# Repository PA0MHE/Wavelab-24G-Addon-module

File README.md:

# Wavelab addon module

Can be used as addon module for the Wavelab 23X1008XP module, which was available during the 2021-2022 timeframe on www.ebay.pl seller:bisonelectronics-sp2jyr
The module converts the first-IF 2364MHz to 432MHz (or 144MHz) , it als generates the required first LO of 1807MHz. It also generates all required DC value, such as 6.5V, +5V, -5V, also the required RX-TX switching is provided. 
The module requires a 10MHz reference signal, it has to be supplied with 7.5V DC. 

# Key components:

HMC213B
2x AS179-92LF
LFB2H2G45SG7C093
2x ADF4351
2x MIC29302
2x BD50HC5MEFJ
ADM7150/1  
ATtiny85-20S  

# PCB

Gerber files are included, PCB's can be ordered at JCL PCB substrate thickness is 0.8mm 

73's Maarten PA0MHE

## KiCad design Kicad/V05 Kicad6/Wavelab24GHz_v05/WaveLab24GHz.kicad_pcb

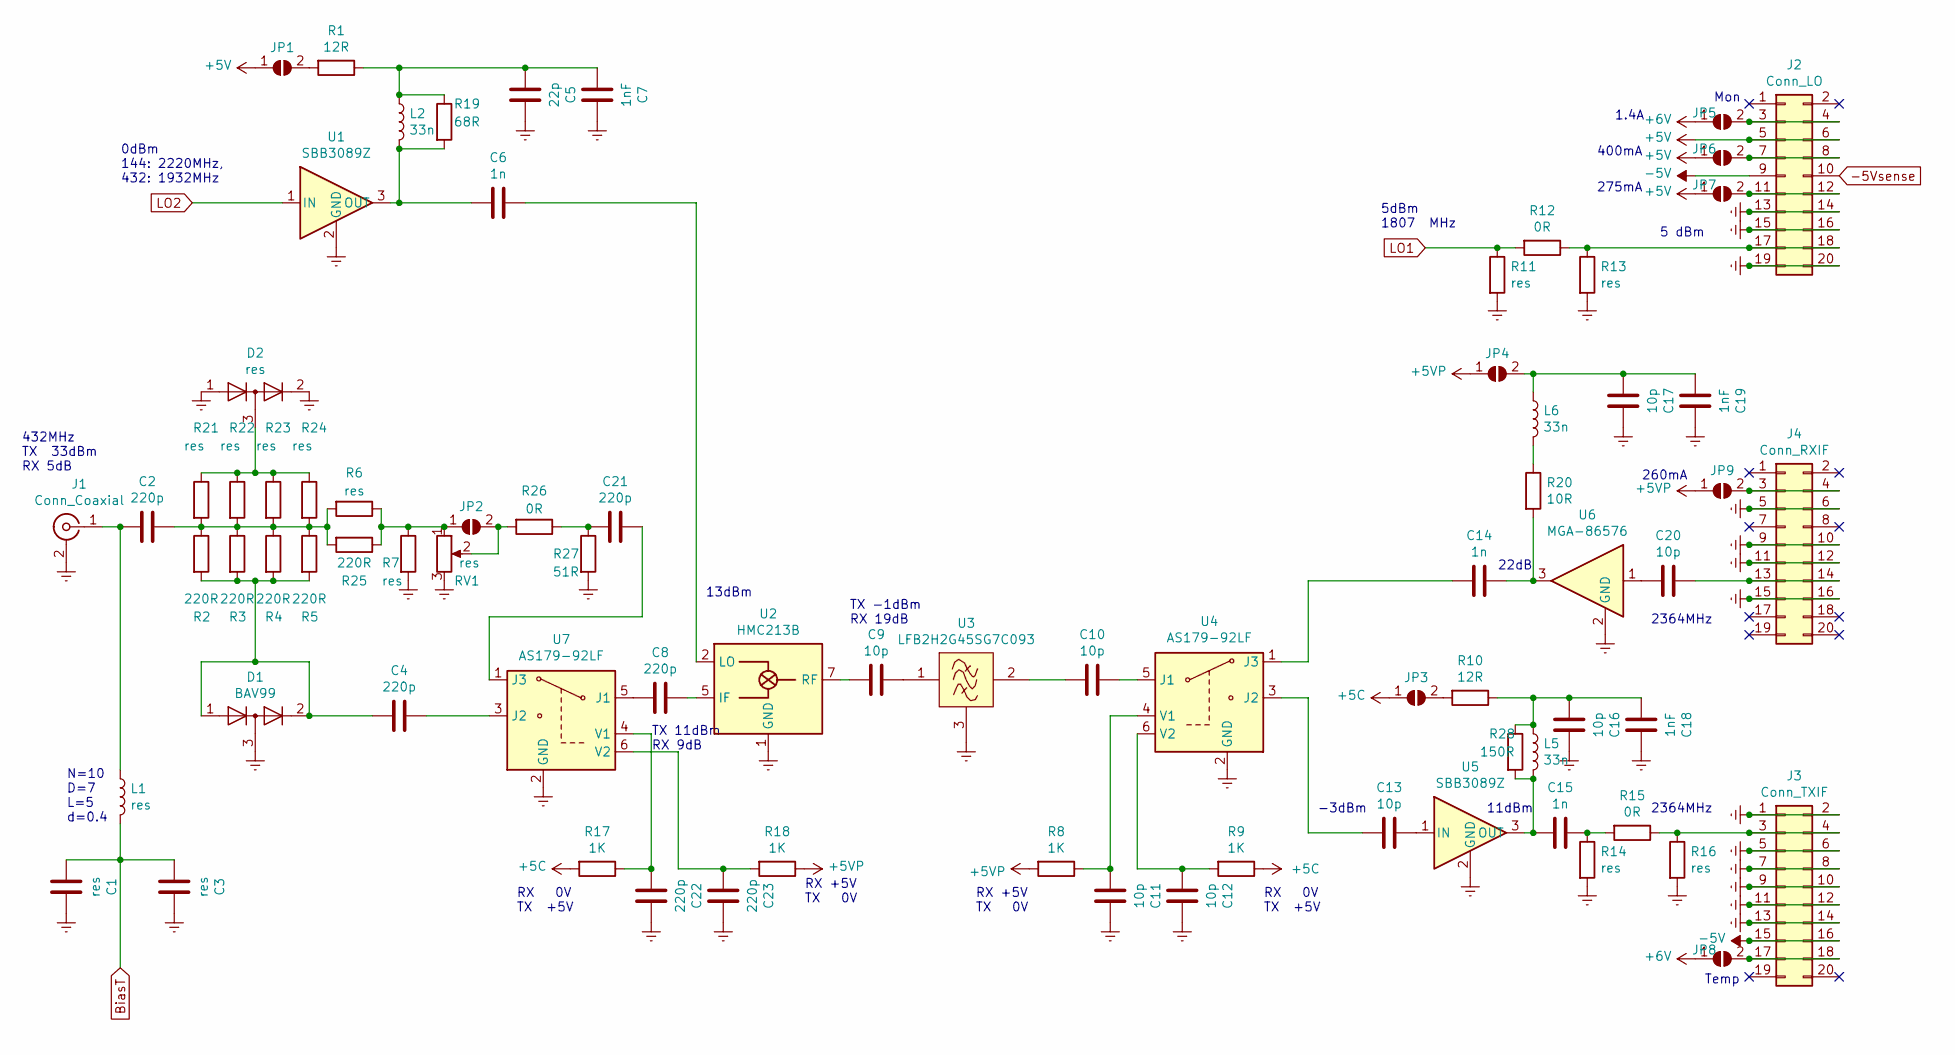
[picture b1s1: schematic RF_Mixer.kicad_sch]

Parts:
C1, C3: res; C_0805_2012Metric_Pad1.18x1.45mm_HandSolder
C2, C4, C8, C21, C22, C23: 220p; C_0805_2012Metric_Pad1.18x1.45mm_HandSolder
C5: 22p; C_0805_2012Metric_Pad1.18x1.45mm_HandSolder
C6, C14, C15: 1n; C_0805_2012Metric_Pad1.18x1.45mm_HandSolder
C7, C18, C19: 1nF; C_0805_2012Metric_Pad1.18x1.45mm_HandSolder
C9, C10, C11, C12, C13, C16, C17, C20: 10p; C_0805_2012Metric_Pad1.18x1.45mm_HandSolder
D1: BAV99; SOT-23
D2: res; SOT-23
J1: Conn_Coaxial; SMA_side_PCB
J2: Conn_LO; PinHeader_24GHz-NP
J3: Conn_TXIF; PinHeader_24GHz-NP
J4: Conn_RXIF; PinHeader_24GHz-NP
JP1, JP2, JP3, JP4, JP5, JP6, JP7, JP8, JP9: S; SolderJumper-2_P1.3mm_Open_RoundedPad1.0x1.5mm
L1: res; AirCoilSMD
L2, L5, L6: 33n; L_0805_2012Metric_Pad1.15x1.40mm_HandSolder
R1, R10: 12R; R_0805_2012Metric_Pad1.20x1.40mm_HandSolder
R2, R3, R4, R5, R25: 220R; R_1206_3216Metric_Pad1.30x1.75mm_HandSolder
R6, R21, R22, R23, R24: res; R_1206_3216Metric_Pad1.30x1.75mm_HandSolder
R7, R11, R13, R14, R16: res; R_0805_2012Metric_Pad1.20x1.40mm_HandSolder
R8, R17, R18: 1K; R_0805_2012Metric_Pad1.20x1.40mm_HandSolder
R9: 1K; R_1206_3216Metric_Pad1.30x1.75mm_HandSolder
R12: 0R; R_1206_3216Metric_Pad1.30x1.75mm_HandSolder
R15, R26: 0R; R_0805_2012Metric_Pad1.20x1.40mm_HandSolder
R19: 68R; R_0805_2012Metric_Pad1.20x1.40mm_HandSolder
R20: 10R; R_0805_2012Metric_Pad1.20x1.40mm_HandSolder
R27: 51R; R_0805_2012Metric_Pad1.20x1.40mm_HandSolder
R28: 150R; R_0805_2012Metric_Pad1.20x1.40mm_HandSolder
RV1: res; Potentiometer_Vishay_TS53YJ_Vertical
U1, U5: SBB3089Z; SOT-89-3
U2: HMC213B; MSOP-8_3x3mm_P0.65mm
U3: LFB2H2G45SG7C093; LFSN25N
U4, U7: AS179-92LF; SOT-363_SC-70-6
U6: MGA-86576

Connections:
+5C: JP3.1 (A), R9.1, R17.2; also elsewhere on the board
+5V: J2.5, J2.6, JP1.1 (A), JP6.1 (A), JP7.1 (A); also elsewhere on the board
+6V: JP5.1 (A), JP8.1 (A); also elsewhere on the board
-5V: J2.9, J3.15, J3.16; also elsewhere on the board
-5Vsense: J2.10; also elsewhere on the board
BiasT: C1.2, C3.2, L1.2; also elsewhere on the board
GNDREF: C1.1, C3.1, C5.1, C7.1, C11.1, C12.1, C16.1, C17.1, C18.1, C19.1, C22.1, C23.1, D1.3 (K), D2.1 (K), D2.2 (A), J1.2 (Ext), J2.13, J2.14, J2.15, J2.16, J2.19, J2.20, J3.1, J3.2, J3.5, J3.6, J3.7, J3.8, J3.9, J3.10, J3.11, J3.12, J3.13, J3.14, J4.5, J4.6, J4.9, J4.10, J4.11, J4.12, J4.15, J4.16, R7.2, R11.2, R13.2, R14.2, R16.2, R27.2, RV1.3, U1.2 (GND), U2.1 (GND), U2.3 (GND), U2.6 (GND), U2.8 (GND), U3.3, U3.4, U4.2 (GND), U5.2 (GND), U6.2 (GND), U7.2 (GND); also elsewhere on the board
LO1: R11.1, R12.2; also elsewhere on the board
LO2: U1.1 (IN); also elsewhere on the board
unnamed: C2.1, R2.1, R3.1, R4.1, R5.1, R6.2, R21.2, R22.2, R23.2, R24.2, R25.2
unnamed: C2.2, J1.1 (In), L1.1
unnamed: C4.1, U7.3 (J2)
unnamed: C4.2, D1.1 (K), D1.2 (A), R2.2, R3.2, R4.2, R5.2
unnamed: C5.2, C7.2, L2.1, R1.1, R19.1
unnamed: C6.1, U2.2 (LO)
unnamed: C6.2, L2.2, R19.2, U1.3 (OUT)
unnamed: C8.1, U2.5 (IF)
unnamed: C8.2, U7.5 (J1)
unnamed: C9.1, U3.1
unnamed: C9.2, U2.7 (RF)
unnamed: C10.1, U4.5 (J1)
unnamed: C10.2, U3.2
unnamed: C11.2, R8.1, U4.4 (V1)
unnamed: C12.2, R9.2, U4.6 (V2)
unnamed: C13.1, U5.1 (IN)
unnamed: C13.2, U4.3 (J2)
unnamed: C14.1, R20.2, U6.3
unnamed: C14.2, U4.1 (J3)
unnamed: C15.1, R14.1, R15.2
unnamed: C15.2, L5.2, R28.2, U5.3 (OUT)
unnamed: C16.2, C18.2, L5.1, R10.1, R28.1
unnamed: C17.2, C19.2, JP4.2 (B), L6.1
unnamed: C20.1, J4.13, J4.14
unnamed: C20.2, U6.1
unnamed: C21.1, U7.1 (J3)
unnamed: C21.2, R26.1, R27.1
unnamed: C22.2, R17.1, U7.4 (V1)
unnamed: C23.2, R18.2, U7.6 (V2)
unnamed: D2.3 (K), R21.1, R22.1, R23.1, R24.1
unnamed: J2.3, J2.4, JP5.2 (B)
unnamed: J2.7, J2.8, JP6.2 (B)
unnamed: J2.11, J2.12, JP7.2 (B)
unnamed: J2.17, J2.18, R12.1, R13.1
unnamed: J3.3, J3.4, R15.1, R16.1
unnamed: J3.17, J3.18, JP8.2 (B)
unnamed: J4.3, J4.4, JP9.2 (B)
unnamed: JP1.2 (B), R1.2
unnamed: JP2.1 (A), R6.1, R7.1, R25.1, RV1.1
unnamed: JP2.2 (B), R26.2, RV1.2
unnamed: JP3.2 (B), R10.2
unnamed: L6.2, R20.1

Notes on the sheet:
TX 11dBm RX 9dB
260mA
Temp
RX +5V TX 0V
275mA
11dBm
-3dBm
432MHz TX 33dBm RX 5dB
22dB
TX -1dBm RX 19dB
1.4A
N=10 D=7 L=5 d=0.4
0dBm 144: 2220MHz, 432: 1932MHz
2364MHz
RX 0V TX +5V
Mon
400mA
13dBm
2364MHz
5 dBm
5dBm 1807 MHz

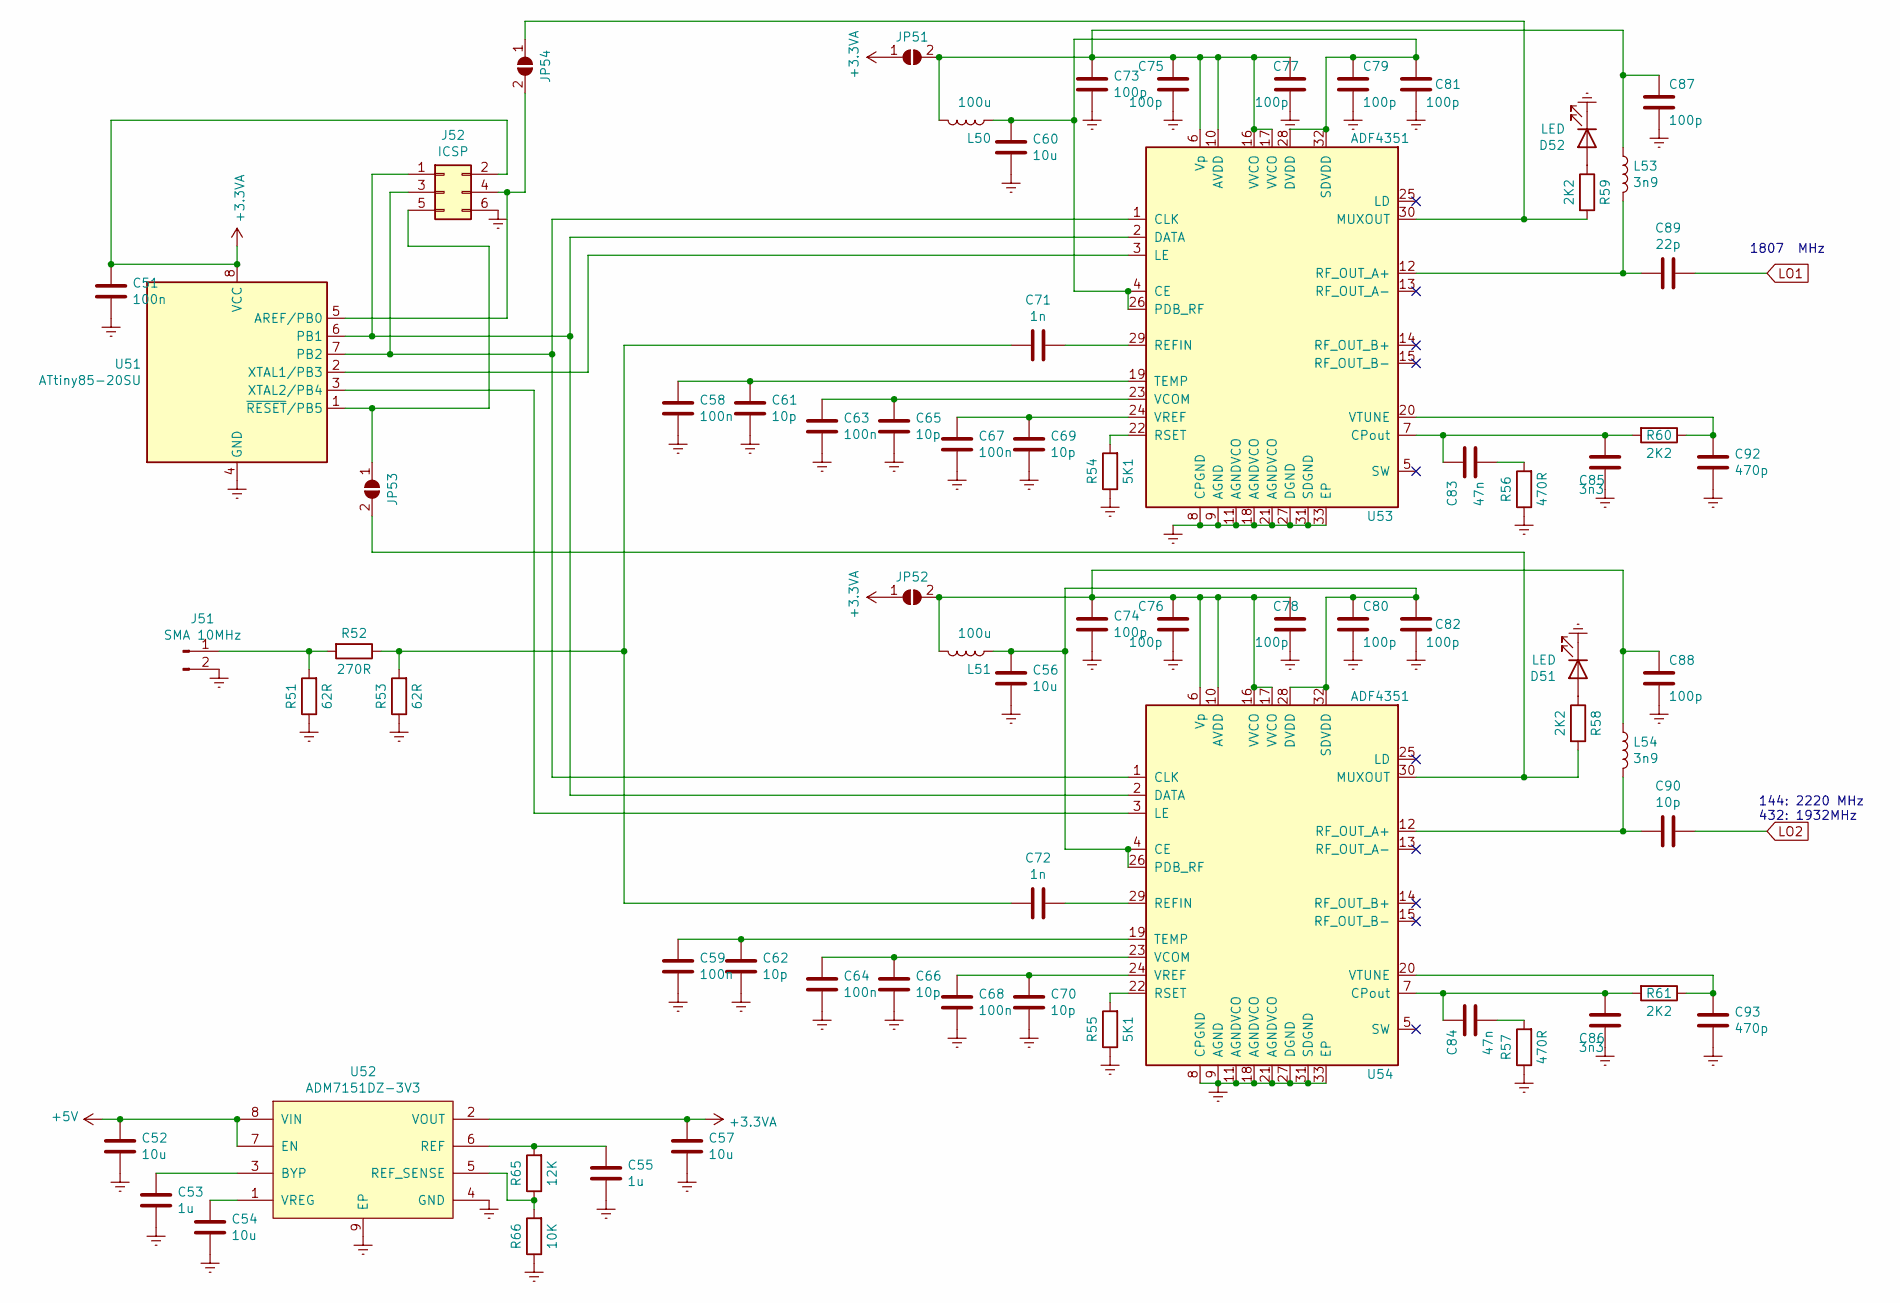
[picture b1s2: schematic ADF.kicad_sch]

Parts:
C51, C58, C59, C63, C64, C67, C68: 100n; C_0805_2012Metric_Pad1.18x1.45mm_HandSolder
C52, C54, C56, C57, C60: 10u; C_0805_2012Metric_Pad1.18x1.45mm_HandSolder
C53, C55: 1u; C_0805_2012Metric_Pad1.18x1.45mm_HandSolder
C61, C62, C65, C66, C69, C70: 10p; C_0603_1608Metric_Pad1.08x0.95mm_HandSolder
C71, C72: 1n; C_0805_2012Metric_Pad1.18x1.45mm_HandSolder
C73, C74, C75, C76, C77, C78, C79, C80, C81, C82: 100p; C_0603_1608Metric_Pad1.08x0.95mm_HandSolder
C83, C84: 47n; C_0805_2012Metric_Pad1.18x1.45mm_HandSolder
C85, C86: 3n3; C_0805_2012Metric_Pad1.18x1.45mm_HandSolder
C87, C88: 100p; C_0805_2012Metric_Pad1.18x1.45mm_HandSolder
C89: 22p; C_0805_2012Metric_Pad1.18x1.45mm_HandSolder
C90: 10p; C_0805_2012Metric_Pad1.18x1.45mm_HandSolder
C92, C93: 470p; C_0805_2012Metric_Pad1.18x1.45mm_HandSolder
D51, D52: LED; LED_0805_2012Metric_Pad1.15x1.40mm_HandSolder
J51: SMA 10MHz; SMA_side_PCB
J52: ICSP; IDC-Header_2x03_P2.54mm_SMD
JP51, JP52, JP53, JP54: S; SolderJumper-2_P1.3mm_Open_RoundedPad1.0x1.5mm
L50, L51: 100u; L_0805_2012Metric_Pad1.05x1.20mm_HandSolder
L53, L54: 3n9; L_0805_2012Metric_Pad1.05x1.20mm_HandSolder
R51, R53: 62R; R_0805_2012Metric_Pad1.20x1.40mm_HandSolder
R52: 270R; R_0805_2012Metric_Pad1.20x1.40mm_HandSolder
R54, R55: 5K1; R_0805_2012Metric_Pad1.20x1.40mm_HandSolder
R56, R57: 470R; R_0805_2012Metric_Pad1.20x1.40mm_HandSolder
R58, R59, R60, R61: 2K2; R_0805_2012Metric_Pad1.20x1.40mm_HandSolder
R65: 12K; R_0805_2012Metric_Pad1.20x1.40mm_HandSolder
R66: 10K; R_0805_2012Metric_Pad1.20x1.40mm_HandSolder
U51: ATtiny85-20SU; SOIJ-8_5.3x5.3mm_P1.27mm
U52: ADM7151DZ-3V3; SOIC-8-1EP_3.9x4.9mm_P1.27mm_EP2.29x3mm_ThermalVias
U53, U54: ADF4351; LFCSP-32-1EP_5x5mm_P0.5mm_EP3.1x3.1mm_ThermalVias

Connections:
+3.3VA: C51.2, C57.2, J52.2, JP51.1 (A), JP52.1 (A), U51.8 (VCC), U52.2 (VOUT)
+5V: C52.2, U52.7 (EN), U52.8 (VIN); also elsewhere on the board
GNDREF: C51.1, C52.1, C53.1, C54.1, C55.1, C56.1, C57.1, C58.1, C59.1, C60.1, C61.1, C62.1, C63.1, C64.1, C65.1, C66.1, C67.1, C68.1, C69.1, C70.1, C73.1, C74.1, C75.1, C76.1, C77.1, C78.1, C79.1, C80.1, C81.1, C82.1, C85.1, C86.1, C87.1, C88.1, C92.1, C93.1, D51.1 (K), D52.1 (K), J51.2, J52.6, R51.1, R53.1, R54.1, R55.1, R56.1, R57.1, R66.1, U51.4 (GND), U52.4 (GND), U52.9 (EP), U53.8 (CPGND), U53.9 (AGND), U53.11 (AGNDVCO), U53.18 (AGNDVCO), U53.21 (AGNDVCO), U53.27 (DGND), U53.31 (SDGND), U53.33 (EP), U54.8 (CPGND), U54.9 (AGND), U54.11 (AGNDVCO), U54.18 (AGNDVCO), U54.21 (AGNDVCO), U54.27 (DGND), U54.31 (SDGND), U54.33 (EP); also elsewhere on the board
LO1: C89.1; also elsewhere on the board
LO2: C90.1; also elsewhere on the board
unnamed: C53.2, U52.3 (BYP)
unnamed: C54.2, U52.1 (VREG)
unnamed: C55.2, R65.2, U52.6 (REF)
unnamed: C56.2, C80.2, C82.2, L51.1, U54.4 (CE), U54.26 (PDB_RF), U54.28 (DVDD), U54.32 (SDVDD)
unnamed: C58.2, C61.2, U53.19 (TEMP)
unnamed: C59.2, C62.2, U54.19 (TEMP)
unnamed: C60.2, C79.2, C81.2, L50.1, U53.4 (CE), U53.26 (PDB_RF), U53.28 (DVDD), U53.32 (SDVDD)
unnamed: C63.2, C65.2, U53.23 (VCOM)
unnamed: C64.2, C66.2, U54.23 (VCOM)
unnamed: C67.2, C69.2, U53.24 (VREF)
unnamed: C68.2, C70.2, U54.24 (VREF)
unnamed: C71.1, U53.29 (REFIN)
unnamed: C71.2, C72.2, R52.1, R53.2
unnamed: C72.1, U54.29 (REFIN)
unnamed: C73.2, C75.2, C77.2, C87.2, JP51.2 (B), L50.2, L53.1, U53.6 (Vp), U53.10 (AVDD), U53.16 (VVCO), U53.17 (VVCO)
unnamed: C74.2, C76.2, C78.2, C88.2, JP52.2 (B), L51.2, L54.1, U54.6 (Vp), U54.10 (AVDD), U54.16 (VVCO), U54.17 (VVCO)
unnamed: C83.1, R56.2
unnamed: C83.2, C85.2, R60.2, U53.7 (CPout)
unnamed: C84.1, R57.2
unnamed: C84.2, C86.2, R61.2, U54.7 (CPout)
unnamed: C89.2, L53.2, U53.12 (RF_OUT_A+)
unnamed: C90.2, L54.2, U54.12 (RF_OUT_A+)
unnamed: C92.2, R60.1, U53.20 (VTUNE)
unnamed: C93.2, R61.1, U54.20 (VTUNE)
unnamed: D51.2 (A), R58.1
unnamed: D52.2 (A), R59.1
unnamed: J51.1, R51.2, R52.2
unnamed: J52.1, U51.6 (PB1), U53.2 (DATA), U54.2 (DATA)
unnamed: J52.3, U51.7 (PB2), U53.1 (CLK), U54.1 (CLK)
unnamed: J52.4, JP54.2 (B), U51.5 (AREF/PB0)
unnamed: J52.5, JP53.1 (A), U51.1 (~RESET/PB5)
unnamed: JP53.2 (B), R58.2, U54.30 (MUXOUT)
unnamed: JP54.1 (A), R59.2, U53.30 (MUXOUT)
unnamed: R54.2, U53.22 (RSET)
unnamed: R55.2, U54.22 (RSET)
unnamed: R65.1, R66.2, U52.5 (REF_SENSE)
unnamed: U51.2 (XTAL1/PB3), U53.3 (LE)
unnamed: U51.3 (XTAL2/PB4), U54.3 (LE)

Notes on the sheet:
1807 MHz
144: 2220 MHz 432: 1932MHz

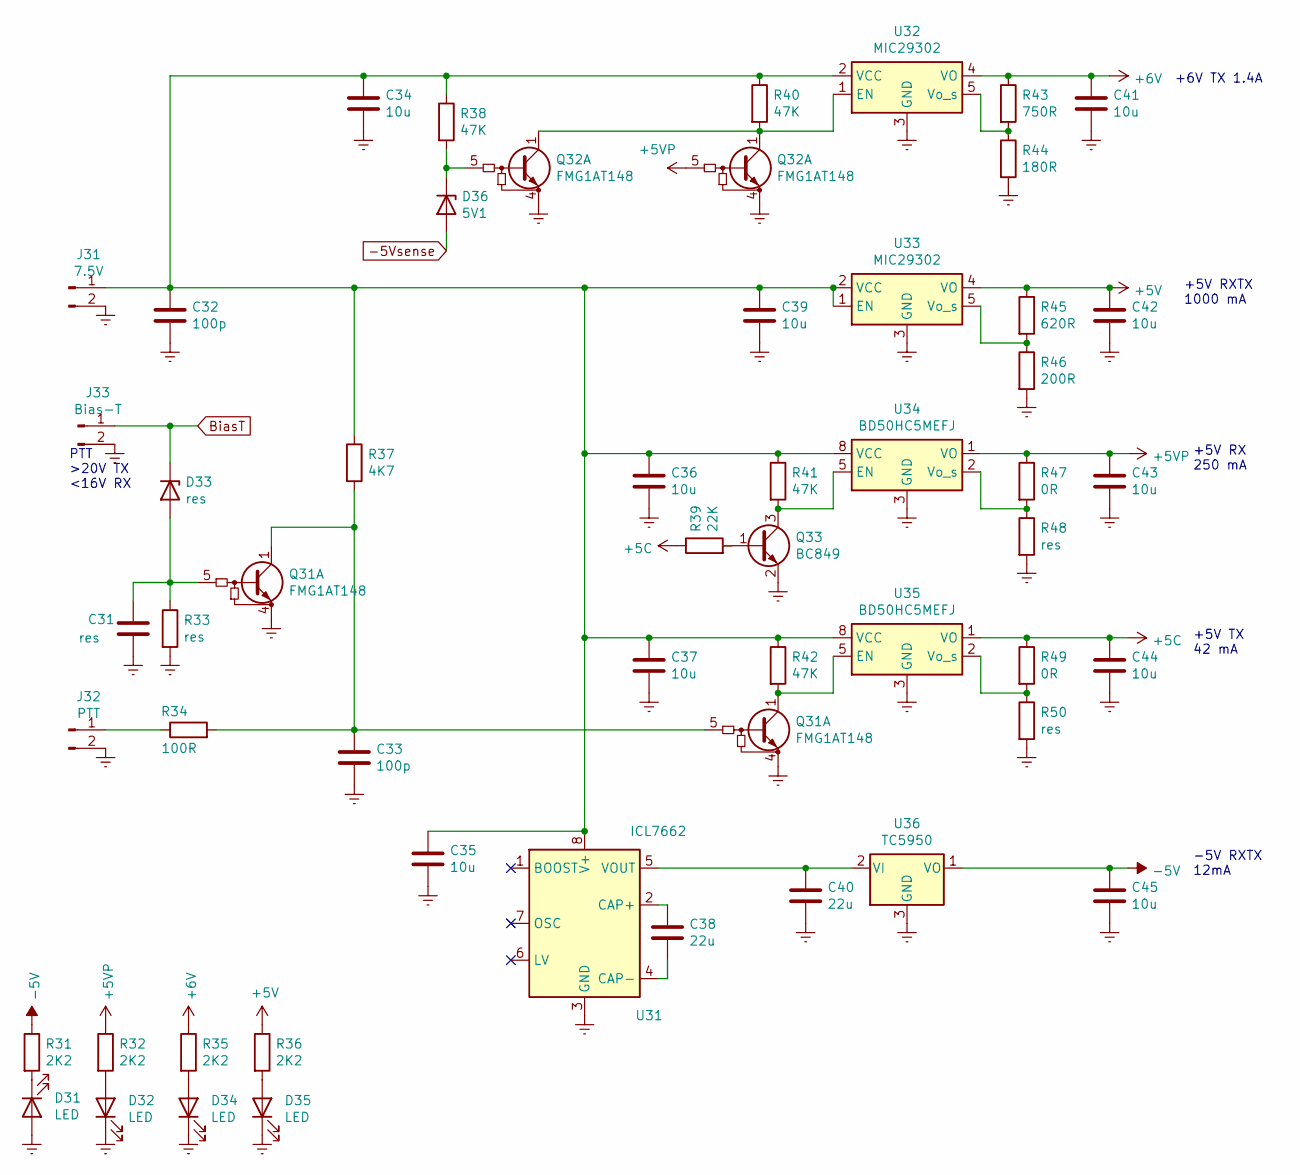
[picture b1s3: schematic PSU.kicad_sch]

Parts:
C31: res; C_0805_2012Metric_Pad1.18x1.45mm_HandSolder
C32, C33: 100p; C_0805_2012Metric_Pad1.18x1.45mm_HandSolder
C34, C35, C36, C37, C39, C41, C42, C43, C44, C45: 10u; C_0805_2012Metric_Pad1.18x1.45mm_HandSolder
C38, C40: 22u; C_0805_2012Metric_Pad1.18x1.45mm_HandSolder
D31, D32, D34, D35: LED; LED_0805_2012Metric_Pad1.15x1.40mm_HandSolder
D33: res; R_0805_2012Metric_Pad1.20x1.40mm_HandSolder
D36: 5V1; R_0805_2012Metric_Pad1.20x1.40mm_HandSolder
J31: 7.5V; KF301-2P-NP
J32: PTT; KF301-2P-NP
J33: Bias-T; KF301-2P-NP
Q31, Q32: FMG1AT148; SOT-25_HandSoldering
Q33: BC849; SOT-23
R31, R32, R35, R36: 2K2; R_0805_2012Metric_Pad1.20x1.40mm_HandSolder
R33, R48, R50: res; R_0805_2012Metric_Pad1.20x1.40mm_HandSolder
R34: 100R; R_0805_2012Metric_Pad1.20x1.40mm_HandSolder
R37: 4K7; R_0805_2012Metric_Pad1.20x1.40mm_HandSolder
R38, R40, R41, R42: 47K; R_0805_2012Metric_Pad1.20x1.40mm_HandSolder
R39: 22K; R_0805_2012Metric_Pad1.20x1.40mm_HandSolder
R43: 750R; R_0805_2012Metric_Pad1.20x1.40mm_HandSolder
R44: 180R; R_0805_2012Metric_Pad1.20x1.40mm_HandSolder
R45: 620R; R_0805_2012Metric_Pad1.20x1.40mm_HandSolder
R46: 200R; R_0805_2012Metric_Pad1.20x1.40mm_HandSolder
R47, R49: 0R; R_0805_2012Metric_Pad1.20x1.40mm_HandSolder
U31: ICL7662; SOIC-8_3.9x4.9mm_P1.27mm
U32, U33: MIC29302; TO-263-5_TabPin6
U34, U35: BD50HC5MEFJ; HTSOP-8-1EP_3.9x4.9mm_P1.27mm_EP2.4x3.2mm
U36: TC5950; SOT-23

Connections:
+5C: C44.1, R39.1, R49.1, U35.1 (VO); also elsewhere on the board
+5V: C42.1, R36.1, R45.1, U33.4 (VO); also elsewhere on the board
+6V: C41.1, R35.1, R43.1, U32.4 (VO); also elsewhere on the board
-5V: C45.1, R31.1, U36.1 (VO); also elsewhere on the board
-5Vsense: D36.2 (A); also elsewhere on the board
BiasT: D33.1 (K), J33.1; also elsewhere on the board
GNDREF: C31.2, C32.2, C33.2, C34.2, C35.2, C36.2, C37.2, C39.2, C40.2, C41.2, C42.2, C43.2, C44.2, C45.2, D31.2 (A), D32.1 (K), D34.1 (K), D35.1 (K), J31.2, J32.2, J33.2, Q31.4 (E1), Q32.4 (E1), Q33.2 (E), R33.2, R44.2, R46.2, R48.2, R50.2, U31.3 (GND), U32.3 (GND), U32.6 (GND), U33.3 (GND), U33.6 (GND), U34.3 (GND), U34.4 (GND), U34.6 (GND), U34.7 (GND), U34.9 (GND), U35.3 (GND), U35.4 (GND), U35.6 (GND), U35.7 (GND), U35.9 (GND), U36.3 (GND); also elsewhere on the board
unnamed: C32.1, C34.1, C35.1, C36.1, C37.1, C39.1, J31.1, R37.1, R38.1, R40.1, R41.1, R42.1, U31.8 (V+), U32.2 (VCC), U33.1 (EN), U33.2 (VCC), U34.8 (VCC), U35.8 (VCC)
unnamed: C38.1, U31.2 (CAP+)
unnamed: C38.2, U31.4 (CAP-)
unnamed: C40.1, U31.5 (VOUT), U36.2 (VI)
unnamed: D31.1 (K), R31.2
unnamed: D32.2 (A), R32.2
unnamed: D34.2 (A), R35.2
unnamed: D35.2 (A), R36.2
unnamed: J32.1, R34.1
unnamed: Q32.1 (C1), Q32.2 (C1), R40.2, U32.1 (EN)
unnamed: Q33.1 (B), R39.2
unnamed: Q33.3 (C), R41.2, U34.5 (EN)
unnamed: R43.2, R44.1, U32.5 (Vo_s)
unnamed: R45.2, R46.1, U33.5 (Vo_s)
unnamed: R47.2, R48.1, U34.2 (Vo_s)
unnamed: R49.2, R50.1, U35.2 (Vo_s)

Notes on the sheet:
+6V TX 1.4A
+5V RX 250 mA
+5V RXTX 1000 mA
PTT >20V TX <16V RX
+5V TX 42 mA
-5V RXTX 12mA

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
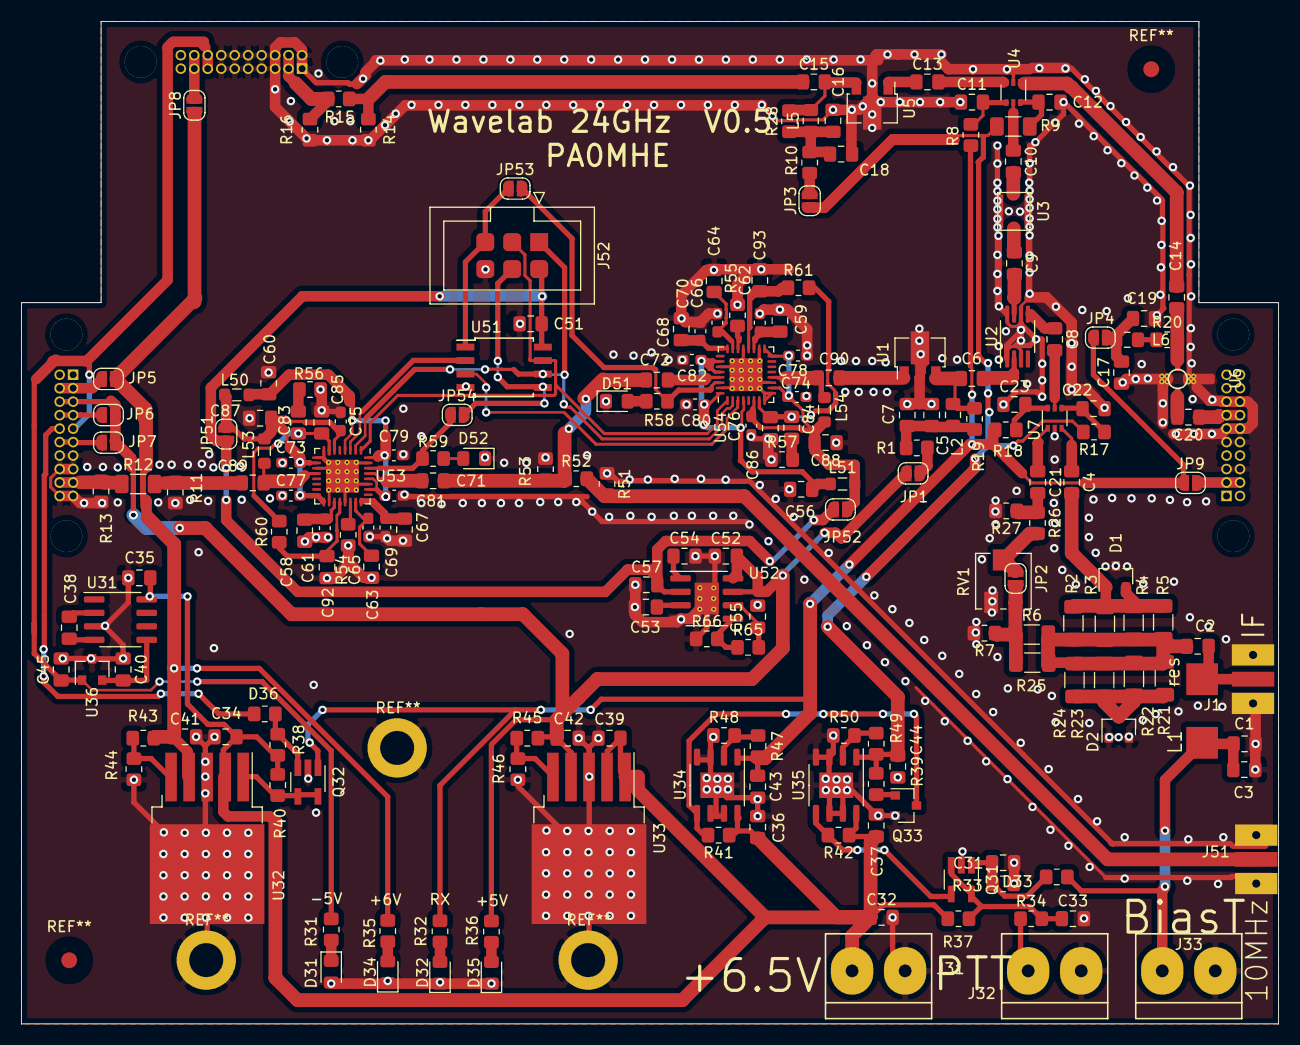
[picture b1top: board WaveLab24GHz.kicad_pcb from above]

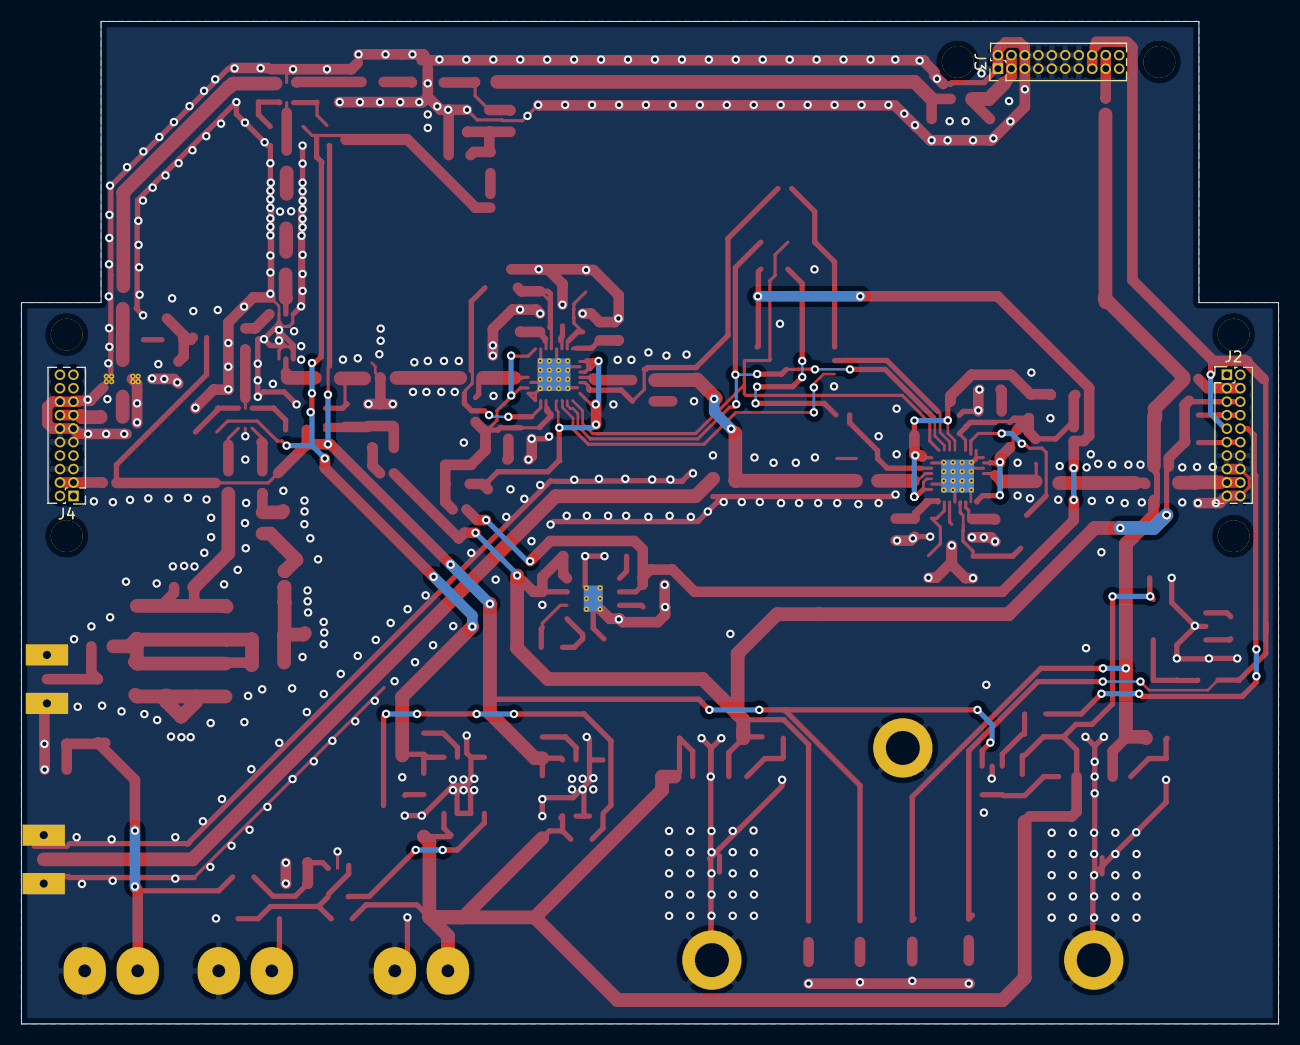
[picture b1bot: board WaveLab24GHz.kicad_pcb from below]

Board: 2 copper layers, 118.5 x 94.5 mm, 202 parts (3 on the bottom side), 111 nets.

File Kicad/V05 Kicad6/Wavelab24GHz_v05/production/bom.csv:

Designator,Footprint,Quantity,Value,LCSC Part #
C1,C_0805_2012Metric_Pad1.18x1.45mm_HandSolder,1,res 1n,
"C10, C11, C12, C13, C16, C17, C20, C9, C90",C_0805_2012Metric_Pad1.18x1.45mm_HandSolder,9,10p,
"C14, C15, C6, C71, C72",C_0805_2012Metric_Pad1.18x1.45mm_HandSolder,5,1n,
"C18, C19, C7",C_0805_2012Metric_Pad1.18x1.45mm_HandSolder,3,1nF,
"C2, C21, C22, C23, C4, C8",C_0805_2012Metric_Pad1.18x1.45mm_HandSolder,6,220p,
C3,C_0805_2012Metric_Pad1.18x1.45mm_HandSolder,1,res 220p,
C31,C_0805_2012Metric_Pad1.18x1.45mm_HandSolder,1,res,
"C32, C33, C87, C88",C_0805_2012Metric_Pad1.18x1.45mm_HandSolder,4,100p,
"C34, C35, C36, C37, C39, C41, C42, C43, C44, C45, C52, C54, C56, C57, C60",C_0805_2012Metric_Pad1.18x1.45mm_HandSolder,15,10u,
"C38, C40",C_0805_2012Metric_Pad1.18x1.45mm_HandSolder,2,22u,
"C5, C89",C_0805_2012Metric_Pad1.18x1.45mm_HandSolder,2,22p,
"C51, C58, C59, C63, C64, C67, C68",C_0805_2012Metric_Pad1.18x1.45mm_HandSolder,7,100n,
"C53, C55",C_0805_2012Metric_Pad1.18x1.45mm_HandSolder,2,1u,
"C61, C62, C65, C66, C69, C70",C_0603_1608Metric_Pad1.08x0.95mm_HandSolder,6,10p,
"C73, C74, C75, C76, C77, C78, C79, C80, C81, C82",C_0603_1608Metric_Pad1.08x0.95mm_HandSolder,10,100p,
"C83, C84",C_0805_2012Metric_Pad1.18x1.45mm_HandSolder,2,47n,
"C85, C86",C_0805_2012Metric_Pad1.18x1.45mm_HandSolder,2,3n3,
"C92, C93",C_0805_2012Metric_Pad1.18x1.45mm_HandSolder,2,470p,
D1,SOT-23,1,BAV99,
D2,SOT-23,1,opt,
"D31, D32, D34, D35, D51, D52",LED_0805_2012Metric_Pad1.15x1.40mm_HandSolder,6,LED,
"D33, R11, R13, R14, R16, R33, R48, R50, R7",R_0805_2012Metric_Pad1.20x1.40mm_HandSolder,9,res,
D36,R_0805_2012Metric_Pad1.20x1.40mm_HandSolder,1,5V1,
J1,SMA_side_PCB,1,Conn_Coaxial,
J2,PinHeader_24GHz-NP,1,Conn_LO,
J3,PinHeader_24GHz-NP,1,Conn_TXIF,
J31,KF301-2P-NP,1,7.5V,
J32,KF301-2P-NP,1,PTT,
J33,KF301-2P-NP,1,Bias-T,
J4,PinHeader_24GHz-NP,1,Conn_RXIF,
J51,SMA_side_PCB,1,SMA 10MHz,
J52,IDC-Header_2x03_P2.54mm_SMD,1,ICSP,
L1,AirCoilSMD,1,res,
"L2, L5, L6",L_0805_2012Metric_Pad1.15x1.40mm_HandSolder,3,33n,
"L50, L51",L_0805_2012Metric_Pad1.05x1.20mm_HandSolder,2,100u,
"L53, L54",L_0805_2012Metric_Pad1.05x1.20mm_HandSolder,2,3n9,
"Q31, Q32",SOT-25_HandSoldering,2,FMG1AT148,
Q33,SOT-23,1,BC849,
"R1, R10",R_0805_2012Metric_Pad1.20x1.40mm_HandSolder,2,12R,
R12,R_1206_3216Metric_Pad1.30x1.75mm_HandSolder,1,0R,
"R15, R26, R47, R49",R_0805_2012Metric_Pad1.20x1.40mm_HandSolder,4,0R,
"R17, R18, R8",R_0805_2012Metric_Pad1.20x1.40mm_HandSolder,3,1K,
R19,R_0805_2012Metric_Pad1.20x1.40mm_HandSolder,1,68R,
"R2, R25, R3, R4, R5",R_1206_3216Metric_Pad1.30x1.75mm_HandSolder,5,220R,
R20,R_0805_2012Metric_Pad1.20x1.40mm_HandSolder,1,10R,
"R21, R22, R23, R24, R6",R_1206_3216Metric_Pad1.30x1.75mm_HandSolder,5,res,
R27,R_0805_2012Metric_Pad1.20x1.40mm_HandSolder,1,51R,
R28,R_0805_2012Metric_Pad1.20x1.40mm_HandSolder,1,150R,
"R31, R32, R35, R36, R58, R59, R60, R61",R_0805_2012Metric_Pad1.20x1.40mm_HandSolder,8,2K2,
R34,R_0805_2012Metric_Pad1.20x1.40mm_HandSolder,1,100R,
R37,R_0805_2012Metric_Pad1.20x1.40mm_HandSolder,1,4K7,
"R38, R40, R41, R42",R_0805_2012Metric_Pad1.20x1.40mm_HandSolder,4,47K,
R39,R_0805_2012Metric_Pad1.20x1.40mm_HandSolder,1,22K,
R43,R_0805_2012Metric_Pad1.20x1.40mm_HandSolder,1,750R,
R44,R_0805_2012Metric_Pad1.20x1.40mm_HandSolder,1,180R,
R45,R_0805_2012Metric_Pad1.20x1.40mm_HandSolder,1,620R,
R46,R_0805_2012Metric_Pad1.20x1.40mm_HandSolder,1,200R,
"R51, R53",R_0805_2012Metric_Pad1.20x1.40mm_HandSolder,2,62R,
R52,R_0805_2012Metric_Pad1.20x1.40mm_HandSolder,1,270R,
"R54, R55",R_0805_2012Metric_Pad1.20x1.40mm_HandSolder,2,5K1,
"R56, R57",R_0805_2012Metric_Pad1.20x1.40mm_HandSolder,2,470R,
R65,R_0805_2012Metric_Pad1.20x1.40mm_HandSolder,1,12K,
R66,R_0805_2012Metric_Pad1.20x1.40mm_HandSolder,1,10K,
R9,R_1206_3216Metric_Pad1.30x1.75mm_HandSolder,1,1K,
RV1,Potentiometer_Vishay_TS53YJ_Vertical,1,res,
"U1, U5",SOT-89-3,2,SBB3089Z,
U2,MSOP-8_3x3mm_P0.65mm,1,HMC213B,
U3,LFSN25N,1,LFB2H2G45SG7C093,
U31,SOIC-8_3.9x4.9mm_P1.27mm,1,ICL7662,
"U32, U33",TO-263-5_TabPin6,2,MIC29302,
"U34, U35",HTSOP-8-1EP_3.9x4.9mm_P1.27mm_EP2.4x3.2mm,2,BD50HC5MEFJ,
U36,SOT-23,1,TC5950,
"U4, U7",SOT-363_SC-70-6,2,AS179-92LF,
U51,SOIJ-8_5.3x5.3mm_P1.27mm,1,ATtiny85-20SU,
U52,SOIC-8-1EP_3.9x4.9mm_P1.27mm_EP2.29x3mm_ThermalVias,1,ADM7151DZ-3V3,
"U53, U54",LFCSP-32-1EP_5x5mm_P0.5mm_EP3.1x3.1mm_ThermalVias,2,ADF4351,
U6,SOT-89-3,1,MGA-86576,

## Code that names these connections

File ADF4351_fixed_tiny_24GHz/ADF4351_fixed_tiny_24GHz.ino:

//  By Maarten PA0MHE 02-01-2022
//******************************************** HARDWARE ********************************************************
//  For ATTINY85 with dual ADF4351:
//  PB0   pin 5   ADF1 MUXout(must be disconnected during programming) No SW to detect yet
//  PB1   pin 6   ADF DAT
//  PB2   pin 7   ADF CLK
//  PB3   pin 2   ADF1 LE (1806 MHz) 
//  PB4   pin 3   ADF2 LE (2220 MHz)
//  PB5   pin 1   ADF2 MUXout (must be disconnected during programming) No SW to detect yet
// 
//  Set the system clock to 1MHz internal.
//******************************************************************************************************************

#include <tinySPI.h>                     // https://github.com/JChristensen/tinySPI

#define ADF1_MUX DDB0
#define ADF1_LE DDB3                     // PIN2 storage register
#define ADF2_MUX DDB5
#define ADF2_LE DDB4                     // PIN3 storage register
#define CLK DDB2
#define DAT DDB1 

uint32_t reg1[6] =  {0x5A0038, 0x8008051, 0x1A004E42, 0x4B3, 0x9A003C, 0x580005} ; // 1807MHz, ref 10MHz x2, 5dBm, Muxout: digital lock detect
//uint32_t reg1[6] =  {0x5A8048, 0x8008051, 0x1A004E42, 0x4B3, 0x9A003C, 0x580005} ; // 1819MHz, ref 10MHz x2, 5dBm, Muxout: digital lock detect
//uint32_t reg2[6] =  {0x378000, 0x8008011, 0x1A004E42, 0x4B3, 0x8A003C, 0x580005} ; // 2m, 2220MHz, ref 10MHz x2, 5dBm, Muxout: digital lock detect
//uint32_t reg2[6] =  { 0x600018, 0x8008029, 0x1A004E42, 0x4B3, 0x9A003C, 0x580005 } ; //438MHz, 1926MHz, ref 10MHz x2, 5dBm, Muxout: digital lock detect 
uint32_t reg2[6] =  {0x608008, 0x8008029, 0x1A004E42, 0x4B3, 0x9A003C, 0x580005} ; // 70cm, 1932MHz, ref 10MHz x2, 5dBm, Muxout: digital lock detect

void setup() {
  SPI.begin();                            // Init SPI bus
  pinMode(ADF1_LE, OUTPUT);               // latch pin needs to be set up
  pinMode(ADF2_LE, OUTPUT);              
  digitalWrite(ADF1_LE, HIGH);
  digitalWrite(ADF2_LE, HIGH);
  pinMode(ADF1_MUX, INPUT);
  pinMode(ADF2_MUX, INPUT);

  delay(1000);                            // Give ADF4351 time to setup

  ADFSet(reg1, ADF1_LE);
  delay(500);
  ADFSet(reg2, ADF2_LE);
  }


void loop(){

} 


void ADFSet(uint32_t reg[6], byte LE) {  // Program all 6 registers ADF4351 
  for (int i = 5; i >= 0; i--) {         // program ADF4351 start with R5
    ADFWriteRegister32(reg[i], LE);
  } 
  delay(1);
  ADFWriteRegister32(reg[0], LE);        // Program R0 again
}


void ADFWriteRegister32(const uint32_t value, byte LE) //Program data into one of the 32bits register, the register that is selected by the four LSBs.
{
  digitalWrite(LE, LOW);
  for (int i = 3; i >= 0; i--)             // loop through 4 x 8bits
  SPI.transfer((value >> 8 * i) & 0xFF);   // shift , mask and send octet via SPI
  digitalWrite(LE, HIGH);                  // Load Enable rising edge the data stored in the shift register
  digitalWrite(LE, LOW);                   // 
}

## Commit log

2022-05-29 Updated schematic
2022-06-03 Added the Kicad project
2022-06-04 Added own made footprints
2022-06-05 Describe how I bring up new module
2022-06-05 Added the HEX files
2022-07-12 Create Wavelab24GHz_v041.zip
    Added Gebers
2022-08-22 Create BOM_v04_2.xlsx
    Updated BOM
2022-08-29 Added some alternative components
2022-11-09 Added production files
2023-01-08 V5 information
2023-01-19 Deleted old V5 project file
